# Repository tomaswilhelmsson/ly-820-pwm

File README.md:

# ly-820-pwm
PWM Addon card for LY-820 PWM DC Motor driver

This card replaces the chip of the LY-820 PWM Board and moves it up to the addon card, enabling both spindle on (Deadtime 100% when no signal) and PWM Input for motor speed control, adjustable by pot on the card.

Designed for +5V signals.

Supposed to be used _without_ the potentiometer connected to LY-820 board.

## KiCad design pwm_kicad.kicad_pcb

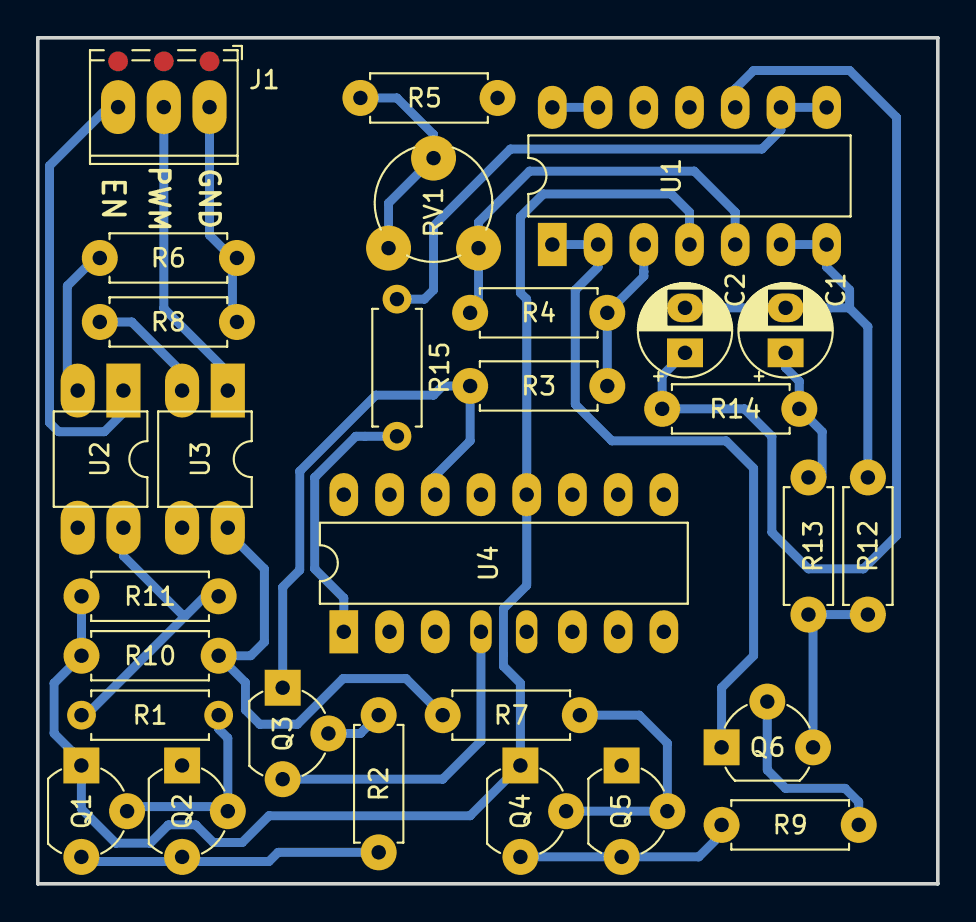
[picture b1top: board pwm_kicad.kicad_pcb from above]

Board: 2 copper layers, 50.0 x 47.0 mm, 29 parts (0 on the bottom side), 28 nets.

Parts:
C1: 1uF; CP_Radial_D5.0mm_P2.50mm
C2: 0.1uF; CP_Radial_D5.0mm_P2.50mm
J1: Screw_Terminal_01x03; TerminalBlock_Phoenix_MPT-0,5-3-2.54_1x03_P2.54mm_Horizontal
Q1, Q4: BC547; TO-92_Wide
Q2, Q5: BC557; TO-92_Wide
Q3, Q6: BS170; TO-92_Wide
R1, R7, R10, R11, R12: 1k; R_Axial_DIN0207_L6.3mm_D2.5mm_P7.62mm_Horizontal
R2, R9: 100; R_Axial_DIN0207_L6.3mm_D2.5mm_P7.62mm_Horizontal
R3: 3.9k; R_Axial_DIN0207_L6.3mm_D2.5mm_P7.62mm_Horizontal
R4: 4.7k; R_Axial_DIN0207_L6.3mm_D2.5mm_P7.62mm_Horizontal
R5: 7.5k; R_Axial_DIN0207_L6.3mm_D2.5mm_P7.62mm_Horizontal
R6, R8, R15: 220; R_Axial_DIN0207_L6.3mm_D2.5mm_P7.62mm_Horizontal
R13: 10k; R_Axial_DIN0207_L6.3mm_D2.5mm_P7.62mm_Horizontal
R14: 100k; R_Axial_DIN0207_L6.3mm_D2.5mm_P7.62mm_Horizontal
RV1: 10k; Potentiometer_Piher_PT-6-V_Vertical
U1: TLC274; DIP-14_W7.62mm_LongPads
U2, U3: PC817; DIP-4_W7.62mm
U4: TL494; DIP-16_W7.62mm_LongPads

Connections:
1IN+: R15.2, U4.1 (1IN+)
DTC: Q3.3 (S), U4.4 (DTC)
DTC_FULL: R1.1, R11.1, U2.4
GND: Q2.1 (C), Q5.1 (C), R5.2, U1.11 (V-), U1.12 (+), U2.3, U3.3, U4.7 (GND)
unnamed: C1.1, R13.2, R14.1
unnamed: C1.2, C2.2, R12.2, U1.6 (-), U1.7
unnamed: C2.1, R14.2, U1.10 (+)
unnamed: J1.1, R6.1, R8.1
unnamed: J1.2, U3.1
unnamed: J1.3, U2.1
unnamed: Q1.2 (B), Q2.2 (B), R1.2
unnamed: Q1.3 (E), Q2.3 (E), R2.1
unnamed: Q3.2 (G), R2.2
unnamed: Q4.2 (B), Q5.2 (B), R7.2
unnamed: Q4.3 (E), Q5.3 (E), R9.1
unnamed: Q6.1 (D), U1.1, U1.2 (-)
unnamed: Q6.2 (G), R9.2
unnamed: Q6.3 (S), R12.1, R13.1
unnamed: R3.2, R4.1, U1.3 (+)
unnamed: R4.2, RV1.1, U1.5 (+)
unnamed: R5.1, RV1.2, RV1.3
unnamed: R6.2, U2.2
unnamed: R8.2, U3.2
unnamed: R15.1, U1.8, U1.9 (-)
unnamed: U1.13 (-), U1.14
PWM_OUT: R7.1, R10.1, U3.4
VCC: Q1.1 (C), Q4.1 (C), R10.2, R11.2, U1.4 (V+), U4.12 (VCC)
VREF: Q3.1 (D), R3.1, U4.14 (REF)

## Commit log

2022-04-09 Add files via upload
    Initial commit
2022-04-09 Update pwm_kicad.kicad_pcb
    Added silkscreen for terminals
